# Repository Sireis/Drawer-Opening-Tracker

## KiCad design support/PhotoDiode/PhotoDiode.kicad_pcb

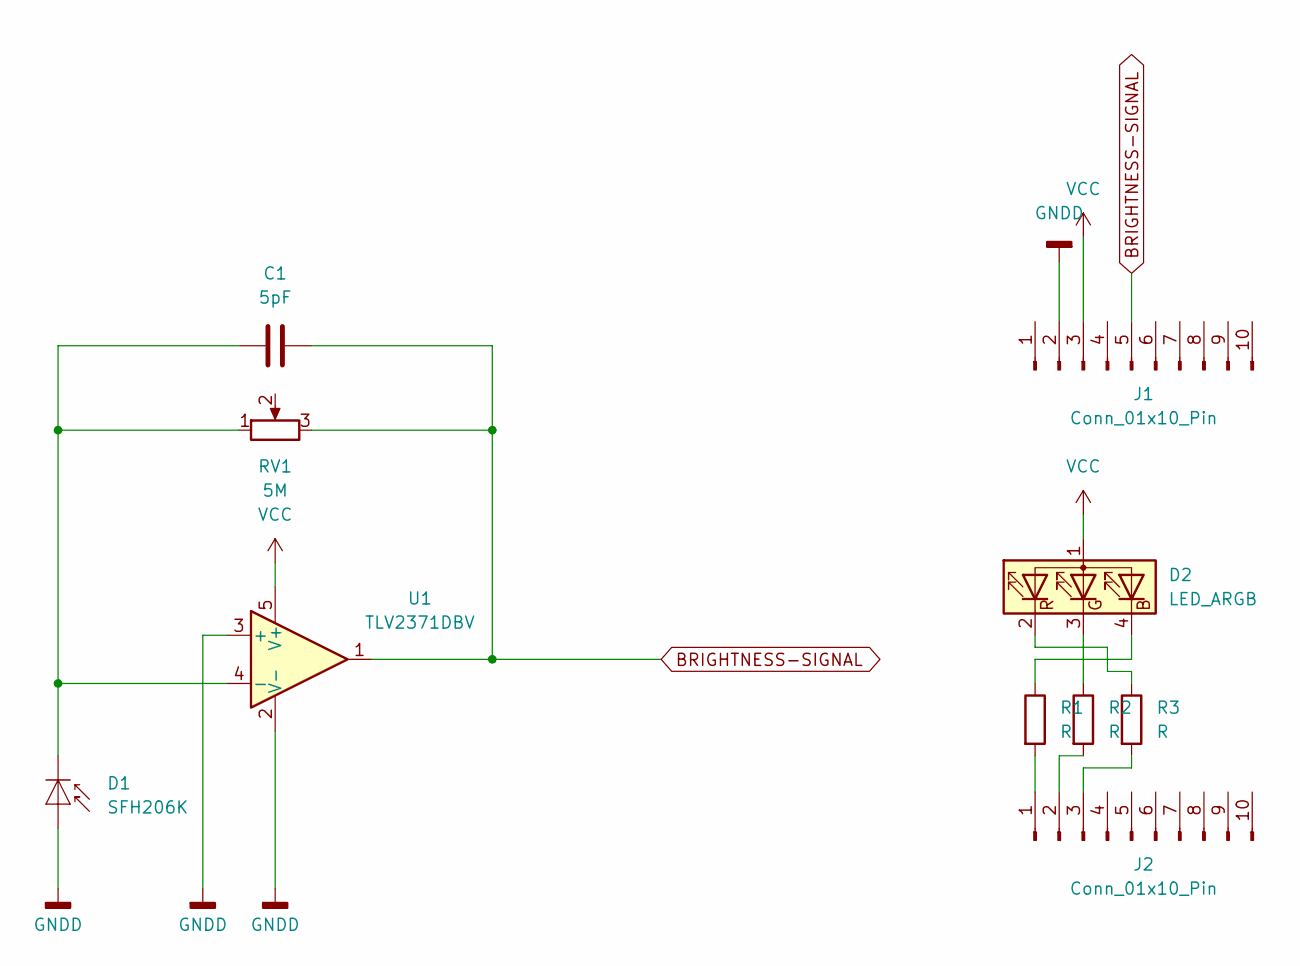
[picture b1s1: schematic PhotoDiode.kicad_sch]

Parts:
C1: 5pF; C_Disc_D3.0mm_W1.6mm_P2.50mm
D1: SFH206K; Osram_SFH205
D2: LED_ARGB; LED_D5.0mm-4_RGB_Staggered_Pins
J1, J2: Conn_01x10_Pin; PinSocket_1x10_P2.54mm_Vertical
R1, R2, R3: R; R_Axial_DIN0204_L3.6mm_D1.6mm_P5.08mm_Horizontal
RV1: 5M; Potentiometer_Bourns_3296W_Vertical
U1: TLV2371DBV; SOT-23-5

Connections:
BRIGHTNESS-SIGNAL: C1.1, J1.5, RV1.3, U1.1
GNDD: D1.2 (A), J1.2, U1.2 (V-), U1.3 (+)
unnamed: C1.2, D1.1 (K), RV1.1, U1.4 (-)
unnamed: D2.4 (BK), R1.1
unnamed: D2.3 (GK), R2.1
unnamed: D2.2 (RK), R3.1
unnamed: J2.1, R1.2
unnamed: J2.2, R2.2
unnamed: J2.3, R3.2
VCC: D2.1 (A), J1.3, U1.5 (V+)

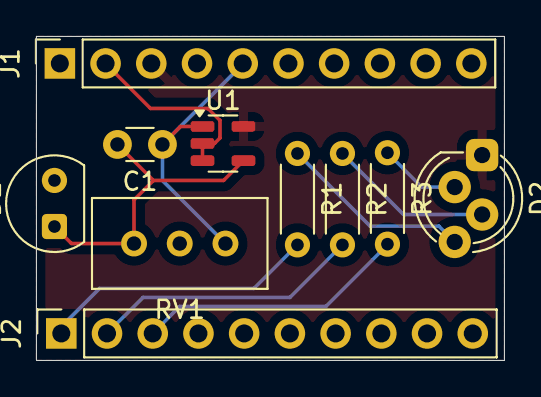
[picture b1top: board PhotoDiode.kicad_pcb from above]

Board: 2 copper layers, 26.0 x 18.0 mm, 10 parts (0 on the bottom side), 10 nets.

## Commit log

2025-04-21 KiCAD project initial
